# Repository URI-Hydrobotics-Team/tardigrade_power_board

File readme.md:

# Power Distribution Board for Tardigrade and Tadpool
A small and simple PCB that offers regulated 5v output for pi, ~9v for jetson, and switchable bus'd power rails for other devices

## Requirements
- 3 seperate 5V output for raspberry pi (USB-C) (switchable)
- 12V output for jetson (switchable)
- switchable battery rail outputs (MiniFit JR)
- power statistics (would be nice to have the ability to measure voltage maybe)
- onboard MCU with serial interface

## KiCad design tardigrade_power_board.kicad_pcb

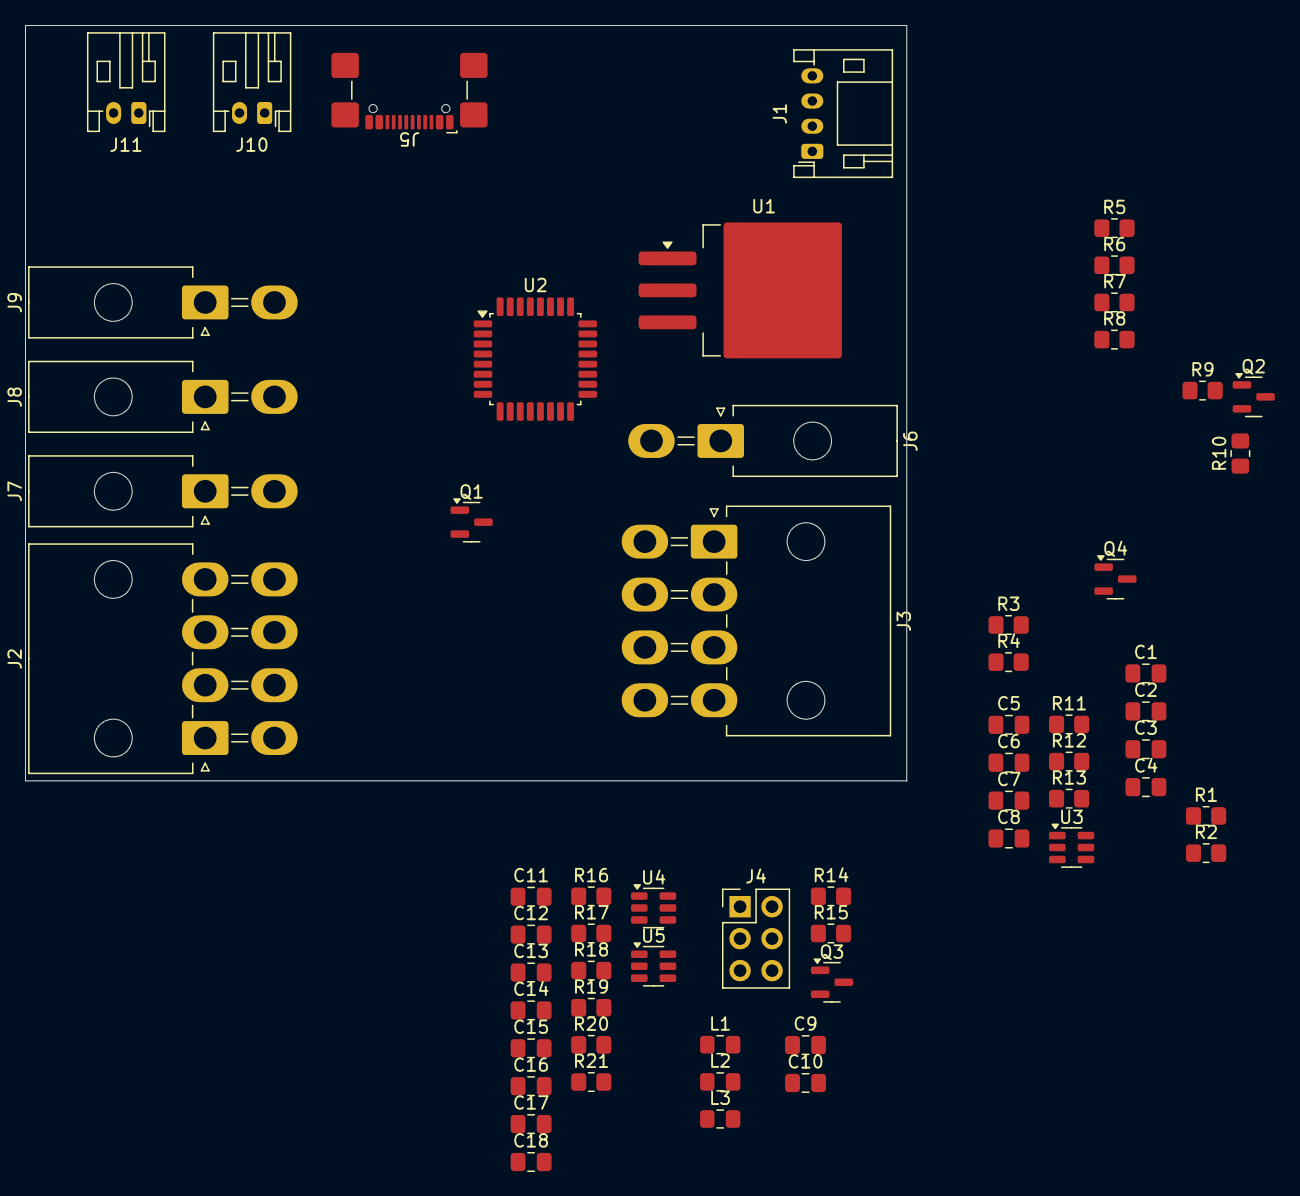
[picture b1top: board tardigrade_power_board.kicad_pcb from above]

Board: 2 copper layers, 70.0 x 60.0 mm, 62 parts (0 on the bottom side), 32 nets, no tracks yet.

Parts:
C1, C2, C3, C4: 22pF; C_0805_2012Metric_Pad1.18x1.45mm_HandSolder
C5, C6, C7, C8, C11, C12, C13, C14, C15, C16, C17, C18: C; C_0805_2012Metric_Pad1.18x1.45mm_HandSolder
C9, C10: 10uF; C_0805_2012Metric_Pad1.18x1.45mm_HandSolder
J1: Conn_01x04_Socket; JST_PH_S4B-PH-K_1x04_P2.00mm_Horizontal
J2, J3: Conn_02x04_Counter_Clockwise; Molex_Mini-Fit_Jr_5569-08A2_2x04_P4.20mm_Horizontal
J4: Conn_02x03_Counter_Clockwise; PinHeader_2x03_P2.54mm_Vertical
J5: USB_C_Receptacle_USB2.0_16P; USB_C_Receptacle_GCT_USB4110
J6, J7, J8, J9: Conn_02x01; Molex_Mini-Fit_Jr_5569-02A2_2x01_P4.20mm_Horizontal
J10, J11: Conn_01x02_Socket; JST_PH_S2B-PH-K_1x02_P2.00mm_Horizontal
L1, L2, L3: L; L_0805_2012Metric_Pad1.15x1.40mm_HandSolder
Q1, Q2, Q3, Q4: AO3400A; SOT-23
R1: 1M; R_0805_2012Metric_Pad1.20x1.40mm_HandSolder
R2: 10K; R_0805_2012Metric_Pad1.20x1.40mm_HandSolder
R3, R4: 5.1k; R_0805_2012Metric_Pad1.20x1.40mm_HandSolder
R5, R8, R10, R13, R15, R16, R19: 10k; R_0805_2012Metric_Pad1.20x1.40mm_HandSolder
R6, R7, R9, R14: 10; R_0805_2012Metric_Pad1.20x1.40mm_HandSolder
R11, R12, R17, R18, R20, R21: R_US; R_0805_2012Metric_Pad1.20x1.40mm_HandSolder
U1: LM1085-12; TO-263-3_TabPin2
U2: ATmega328P-A; TQFP-32_7x7mm_P0.8mm
U3, U4, U5: AP62300TWU; TSOT-23-6

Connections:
+5V: C3.1, C4.2, R2.1, U2.4 (VCC), U2.6 (VCC), U2.18 (AVCC)
+12V: C10.1, J6.2, U1.2 (VO)
/5V_ALT1_VBUS: C13.1, C14.1, J10.2, L2.2, R17.1
/5V_ALT2_VBUS: C17.1, C18.1, J11.2, L3.2, R20.1
/12V_SINK: J6.1, Q3.3 (D)
/MCU_RESET: R2.2, U2.29 (~RESET/PC6)
/Microcontroller/XTAL1: C1.1, R1.1, U2.7 (XTAL1/PB6)
/Microcontroller/XTAL2: C2.1, R1.2, U2.8 (XTAL2/PB7)
/PI_VBUS: C7.1, C8.1, J5.A4 (VBUS), J5.A9 (VBUS), J5.B4 (VBUS), J5.B9 (VBUS), L1.2, R11.1
/Switched +5V Outputs/5V_EN1: R13.1, U3.5 (EN)
/Switched +5V Outputs/5V_EN2: R16.1, U4.5 (EN)
/Switched +5V Outputs/5V_EN3: R19.1, U5.5 (EN)
GND: C1.2, C2.2, C3.2, C4.1, C5.2, C7.2, C9.2, C10.2, C11.2, C14.2, C15.2, C18.2, J1.1, J2.1, J2.2, J2.3, J2.4, J3.1, J3.2, J3.3, J3.4, J5.A1 (GND), J5.A12 (GND), J5.B1 (GND), J5.B12 (GND), J5.S1 (SHIELD), J10.1, J11.1, Q1.2 (S), Q2.2 (S), Q3.2 (S), Q4.2 (S), R3.2, R4.2, R5.2, R8.2, R10.2, R12.2, R13.2, R15.2, R16.2, R18.2, R19.2, R21.2, U1.1 (GND), U2.3 (GND), U2.5 (GND), U2.21 (GND), U3.1 (GND), U4.1 (GND), U5.1 (GND)
unnamed: J5.A5 (CC1), R3.1
unnamed: J5.B5 (CC2), R4.1
unnamed: J7.1, Q4.3 (D)
unnamed: J8.1, Q1.3 (D)
unnamed: J9.1, Q2.3 (D)
unnamed: Q1.1 (G), R7.2, R8.1
unnamed: Q2.1 (G), R9.2, R10.1
unnamed: Q3.1 (G), R14.2, R15.1
unnamed: Q4.1 (G), R5.1, R6.2
unnamed: C6.1, U3.6 (BST)
unnamed: C8.2, R11.2, R12.1, U3.4 (FB)
unnamed: C6.2, L1.1, U3.2 (SW)
unnamed: C12.1, U4.6 (BST)
unnamed: C13.2, R17.2, R18.1, U4.4 (FB)
unnamed: C12.2, L2.1, U4.2 (SW)
unnamed: C16.1, U5.6 (BST)
unnamed: C17.2, R20.2, R21.1, U5.4 (FB)
unnamed: C16.2, L3.1, U5.2 (SW)
VBAT: C5.1, C9.1, C11.1, C15.1, J2.5, J2.6, J2.7, J2.8, J3.5, J3.6, J3.7, J3.8, J7.2, J8.2, J9.2, U1.3 (VI), U3.3 (IN), U4.3 (IN), U5.3 (IN)
